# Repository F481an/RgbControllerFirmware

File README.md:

The Set and respons Topics can be set with the defines in the defiens.h File

```c++
#define statusTopic "bedroom/UnderBedLight/light/set"
#define BrightnessTopic "bedroom/UnderBedLight/brightness/set"
#define rgbTopic "bedroom/UnderBedLight/rgb/set"

#define statusResponseTopic "bedroom/UnderBedLight/light/status"
#define BrightnessResponseTopic "bedroom/UnderBedLight/brightness/status"
#define rgbResponseTopic "bedroom/UnderBedLight/rgb/status"
```

This is a working example for the configguration in HomeAssistant
```c++
light:
  - platform: mqtt
    name: "UnderBedLight"
    command_topic: "bedroom/UnderBedLight/light/set"
    brightness_command_topic: "bedroom/UnderBedLight/brightness/set"
    rgb_command_topic: "bedroom/UnderBedLight/rgb/set"
    state_topic: "bedroom/UnderBedLight/light/status"
    brightness_state_topic: "bedroom/UnderBedLight/brightness/status"
    rgb_state_topic: "bedroom/UnderBedLight/rgb/status"
    payload_on: "ON"
    payload_off: "OFF"
    optimistic: false
```

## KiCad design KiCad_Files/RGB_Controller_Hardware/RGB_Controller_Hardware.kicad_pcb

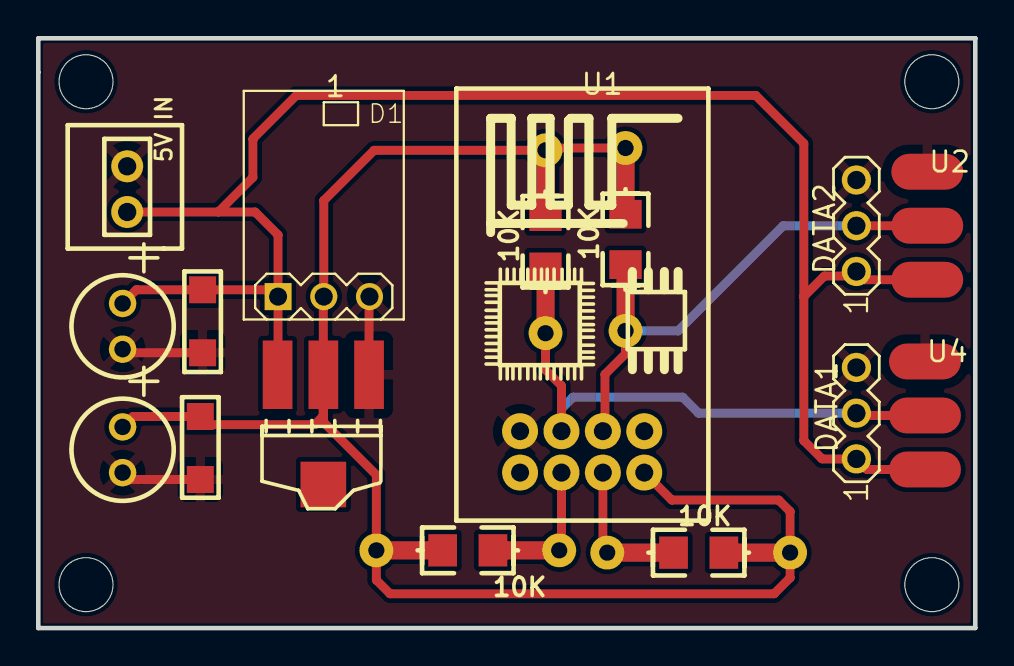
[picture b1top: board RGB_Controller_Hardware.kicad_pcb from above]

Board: 2 copper layers, 52.1 x 32.8 mm, 16 parts (0 on the bottom side), 7 nets.

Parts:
1: D1; REG-AMS1117-3P
C2, C3: CAPACITOR-SMD-0.1uF; CAPACITOR-SMD
DATA1, DATA2: 1; 3PIN-HEADER
P1: 5V IN
R1, R2, R3, R4: 10K; AXIAL-0.4 10K
U1: ESP8266 MINI; ESP8266
U2, U4: 3Pin-Neopixel; 3PIN-10MM-LED-STRIP
U3: AMS1117
U7, U9: +; CAPACITOR_I

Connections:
3V3: 1.2, C3.2, R1.2, R2.2, R3.2, R4.2, U1.8, U3.2, U7.1
+5V: 1.1, C2.1, DATA1.1, DATA2.1, P1.1, U2.3, U3.3, U4.3, U9.1
GND: 1.3, C2.2, C3.1, DATA1.3, DATA2.3, P1.2, U1.1, U2.1, U3.1, U4.1, U7.2, U9.2
LED_DATA_1: DATA1.2, R1.1, U1.2, U4.2
LED_DATA_2: DATA2.2, R2.1, U1.3, U2.2
U1_6: R3.1, U1.6
U1_7: R4.1, U1.7

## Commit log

2021-12-02 init
2021-12-03 ota Working basic api working
2021-12-04 time will now be updatet with ntp
2021-12-04 turn on and off each strip per json massage
2021-12-05 get time from NTP server added things that neet tbd
2021-12-09 im plemented automatic on of switching
2021-12-12 set fix ip address
2021-12-15 changed ip adresse to upload and chanded amound of leds
2021-12-17 changed names of variables
2021-12-18 switched to a rgb strip object changed domains for data removed ntp temporaly
2021-12-18 changed host names
2021-12-28 removed time
2021-12-28 added basic mqtt
2021-12-29 mqtt now working
2022-01-01 brightness controll is now working
2022-01-01 added auto reconect if connetion to mqtt server ist lost
2022-04-02 done some refactoring
2022-04-02 now publishing currant status over mqtt
2022-04-02 now saving values to eepom and loading on bootup
2022-04-03 changed response topic to status
2022-04-13 added a readme with most importand commands
2022-07-03 added logic to abord the connection to the mqtt server if for some reason it is not avaible
2023-01-30 done refactoring
2023-01-31 added Kicad Files
2023-03-06 changed to domain
2023-03-08 changed dns ip
